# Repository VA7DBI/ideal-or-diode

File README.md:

# Ideal OR Diode

In realms where reliability reigns supreme,
Systems of high avail strive to dream,
With power supplies redundant and true,
Bolstering reliability, ensuring they pursue.

Tradition has seen diodes stand tall,
Linked with capacitors to answer the call,
Yet, in their shadow, a drawback doth lie,
With voltage drop, power loss doth vie.

Enter now, with grace and might,
A solution born of innovation's light,
An N-channel MOSFET, a hero untold,
Bringing forth efficiency, breaking the mold.

Activated in power's fervent dance,
It shuns the loss, it takes its chance,
With low voltage drop, it carries the load,
Matching ideals, along wisdom's road.

Thus, in the realm where technology thrives,
Poetry meets innovation, where beauty thrives,
In systems of power, reliability finds its place,
A tale of progress, a poetic grace.

## Summary

This Ideal OR Diode circuit is designed to protect a 12V nominal (5-15) supply at 50A.

### Images

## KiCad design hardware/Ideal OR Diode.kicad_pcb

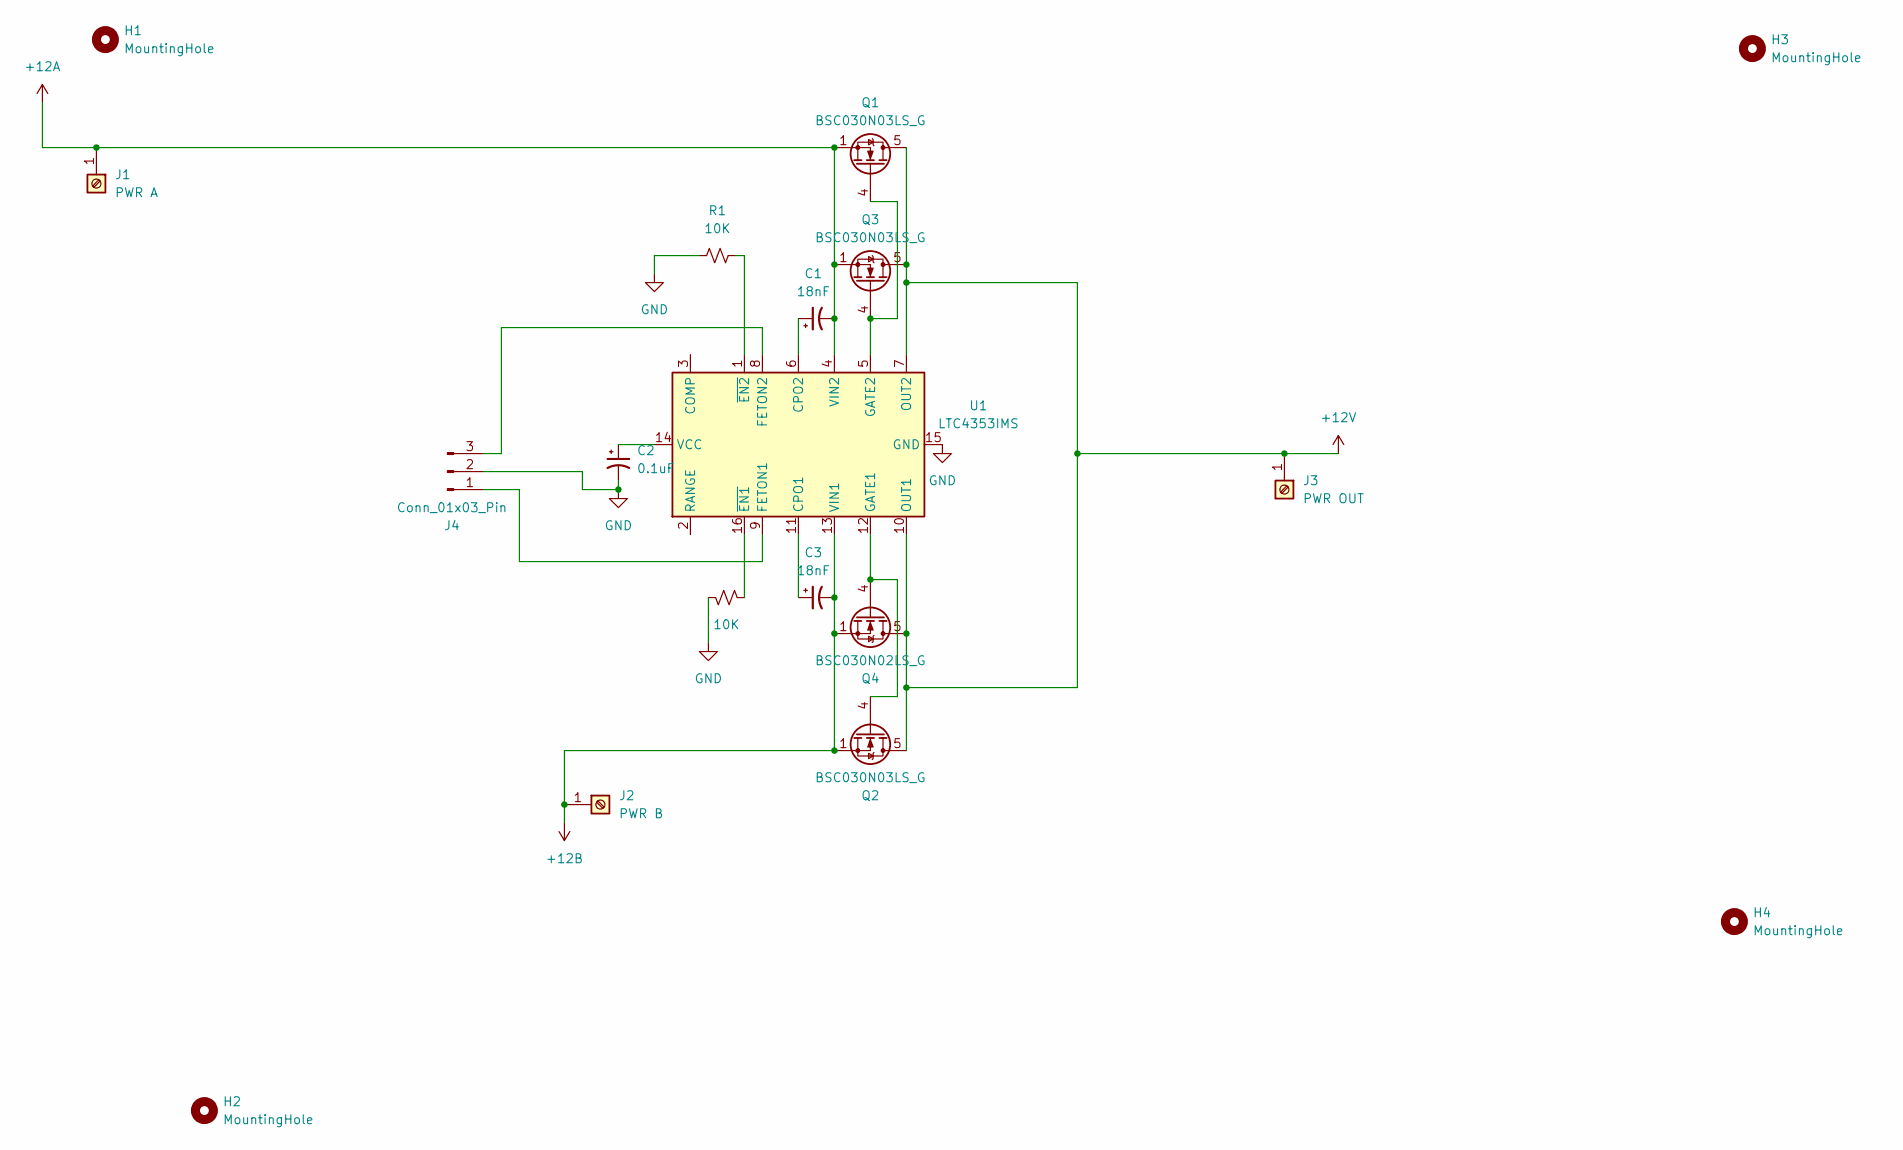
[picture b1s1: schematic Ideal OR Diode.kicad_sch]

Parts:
C1, C3: 18nF; C_0603_1608Metric_Pad1.08x0.95mm_HandSolder
C2: 0.1uF; C_0603_1608Metric_Pad1.08x0.95mm_HandSolder
H1, H2, H3, H4: MountingHole; MountingHole_2.2mm_M2
J1: PWR A; TerminalBlock_MetzConnect_360425_1x01_Horizontal_ScrewM4.0_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
J2: PWR B; TerminalBlock_MetzConnect_360425_1x01_Horizontal_ScrewM4.0_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
J3: PWR OUT; TerminalBlock_MetzConnect_360425_1x01_Horizontal_ScrewM4.0_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
J4: Conn_01x03_Pin; PinHeader_1x03_P1.00mm_Vertical
Q1, Q2, Q3: BSC030N03LS_G; Infineon_PG-TDSON-8_6.15x5.15mm
Q4: BSC030N02LS_G; Infineon_PG-TDSON-8_6.15x5.15mm
R1, R2: 10K; R_0603_1608Metric_Pad0.98x0.95mm_HandSolder
U1: LTC4353IMS; MSOP-16_3x4mm_P0.5mm

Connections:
+12A: C1.2, J1.1, Q1.1 (S), Q1.2 (S), Q1.3 (S), Q3.1 (S), Q3.2 (S), Q3.3 (S), U1.4 (VIN2)
+12B: C3.2, J2.1, Q2.1 (S), Q2.2 (S), Q2.3 (S), Q4.1 (S), Q4.2 (S), Q4.3 (S), U1.13 (VIN1)
+12V: J3.1, Q1.5 (D), Q2.5 (D), Q3.5 (D), Q4.5 (D), U1.7 (OUT2), U1.10 (OUT1)
GND: C2.2, J4.2, R1.1, R2.1, U1.15 (GND)
unnamed: J4.1, U1.9 (FETON1)
unnamed: J4.3, U1.8 (FETON2)
unnamed: Q1.4 (G), Q3.4 (G), U1.5 (GATE2)
unnamed: Q2.4 (G), Q4.4 (G), U1.12 (GATE1)
unnamed: C3.1, U1.11 (CPO1)
unnamed: C1.1, U1.6 (CPO2)
unnamed: C2.1, U1.14 (VCC)
unnamed: R2.2, U1.16 (~EN1)
unnamed: R1.2, U1.1 (~EN2)

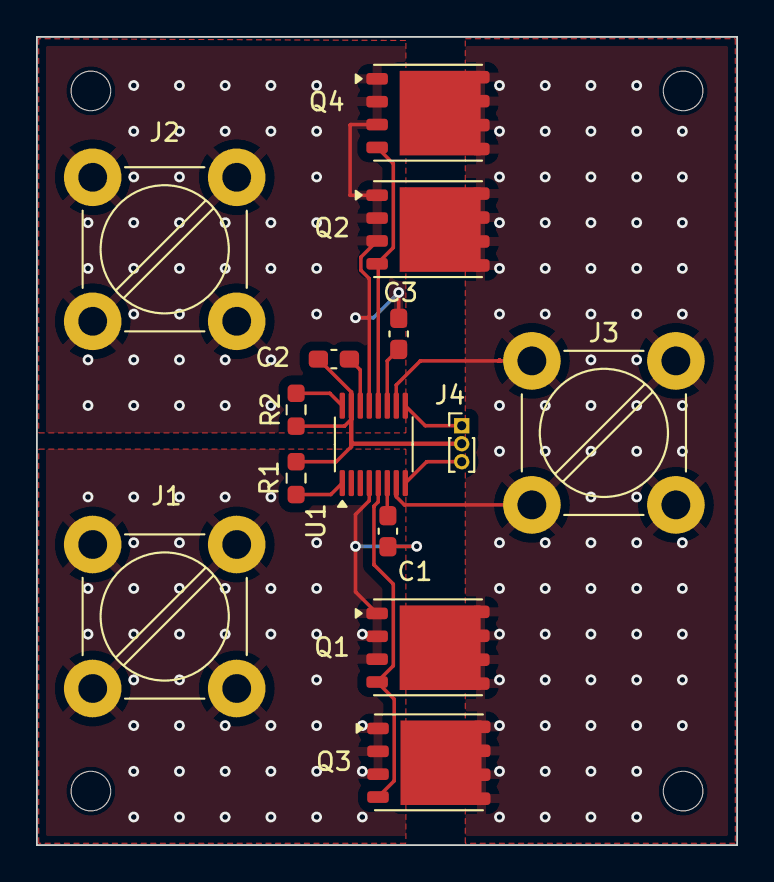
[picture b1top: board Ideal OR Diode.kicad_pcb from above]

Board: 2 copper layers, 38.9 x 44.9 mm, 18 parts (0 on the bottom side), 13 nets.

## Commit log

2024-04-10 Initial check in of kiCad8 project
2024-04-10 Readme and CI
2024-04-10 Fix typo pcb_image.yaml
2024-04-10 Update pcb_image.yaml
    remove / in pcb_file
2024-04-11 act on the PCB file, not the Project
2024-04-11 fix URL in readme
2024-04-11 Update the Sheet frames to show URL
2024-04-11 Produce JLPCB gerbers
2024-04-11 Fix kibot to use the correct action image
2024-04-11 Use the correct filename
2024-04-11 ensure to checkout the kicad_sch files
2024-04-11 Follow newer excample for kibot CI
2024-04-11 Example is poor, add come clarity
2024-04-16 Update via-stiching
